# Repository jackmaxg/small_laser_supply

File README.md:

# Swept Source Laser Driver

A small 5v 3mA constant current laser diode power supply for the Physical Optics and Electronics lab, MIT RLE.

Jackson Gray

jackmaxg@mit.edu

Summer '18 UROP

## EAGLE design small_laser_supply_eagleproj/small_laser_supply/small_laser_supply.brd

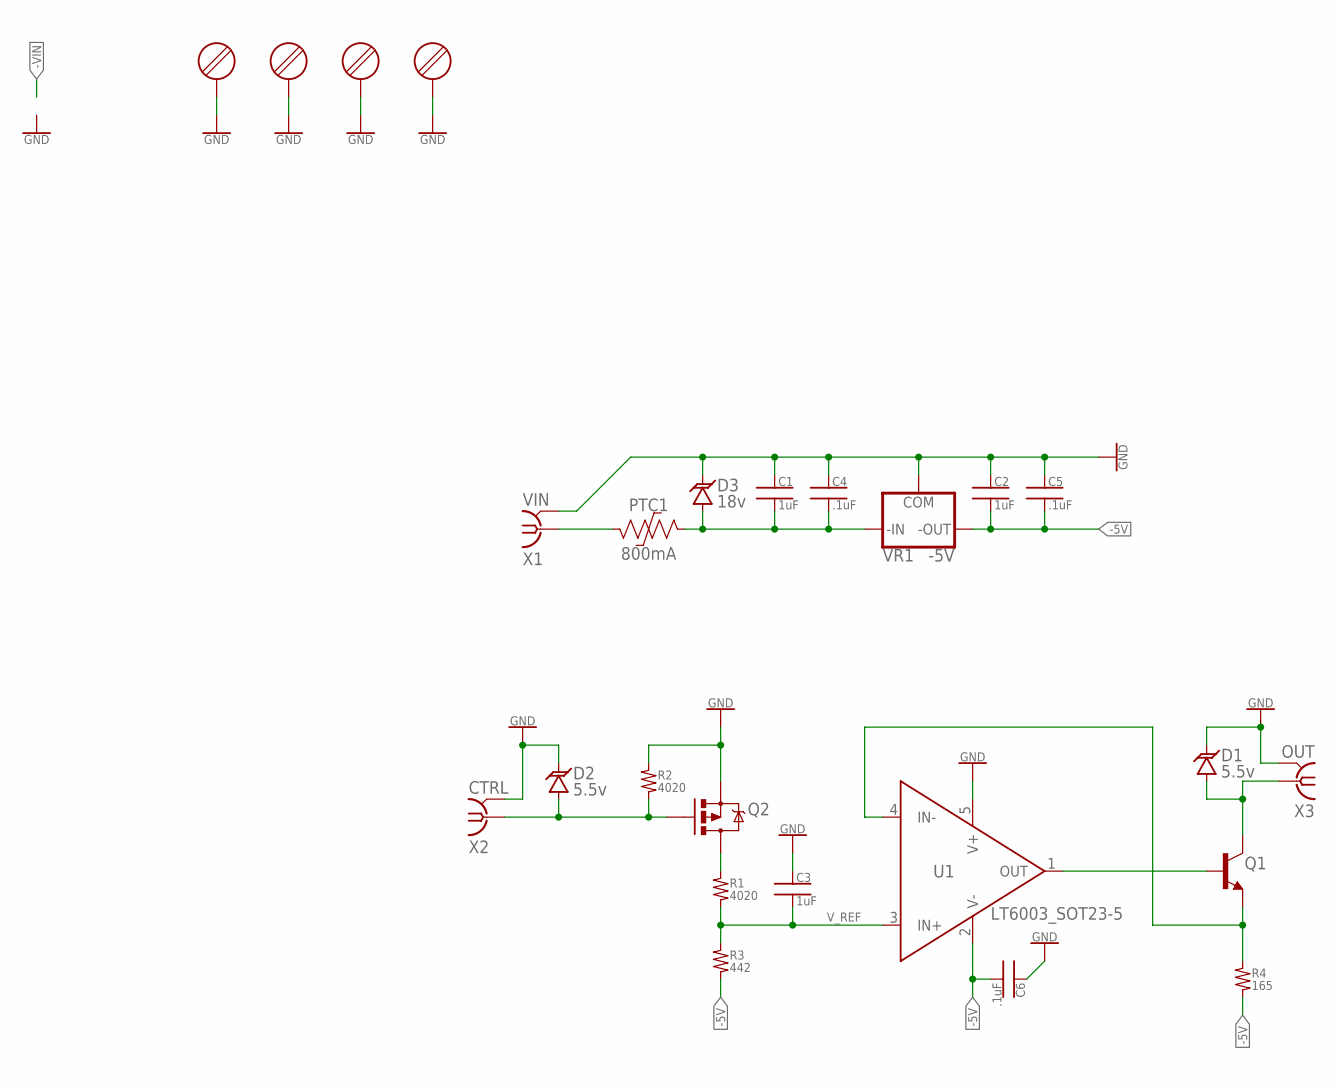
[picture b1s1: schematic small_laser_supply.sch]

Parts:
C1, C2, C3: 1uF; 0603
C4, C5, C6: .1uF; 0603
D1, D2: 5.5v; DO-214AA
D3: 18v; DO-214AA
MH1, MH2, MH3, MH4: THREADED_INSERT_M3; 7466003R
PTC1: 800mA; 2SMD_PTC
Q1: BJT_NPN_SOT23-3; SOT23-3
Q2: MOSFET_P-CHANNEL_SOT23-3; SOT23-3
R1, R2: 4020; 0603
R3: 442; 0603
R4: 165; 0603
U1: LT6003_SOT23-5; SOT23-5
VR1: -5V; DPAK
X1: VIN; 5-1634503-1
X2: CTRL; 5-1634503-1
X3: OUT; 5-1634503-1

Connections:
-5V: C2.2, C5.2, C6.2, R3.2, R4.2, U1.2 (V-), VR1.3 (OUT)
GND: C1.1, C2.1, C3.1, C4.1, C5.1, C6.1, D1.C, D2.C, D3.C, MH1.P, MH2.P, MH3.P, MH4.P, Q2.2 (S), R2.1, U1.5 (V+), VR1.1 (GND), X1.G1 (GND), X1.G2 (GND), X1.G3 (GND), X1.G4 (GND), X2.G1 (GND), X2.G2 (GND), X2.G3 (GND), X2.G4 (GND), X3.G1 (GND), X3.G2 (GND), X3.G3 (GND), X3.G4 (GND)
unnamed: Q1.1 (B), U1.1 (OUT)
unnamed: Q1.2 (E), R4.1, U1.4 (IN-)
unnamed: Q2.3 (D), R1.1
unnamed: PTC1.1, X1.C (1)
unnamed: D1.A, Q1.3 (C), X3.C (1)
unnamed: C1.2, C4.2, D3.A, PTC1.2, VR1.4 (IN)
unnamed: D2.A, Q2.1 (G), R2.2, X2.C (1)
V_REF: C3.2, R1.2, R3.1, U1.3 (IN+)

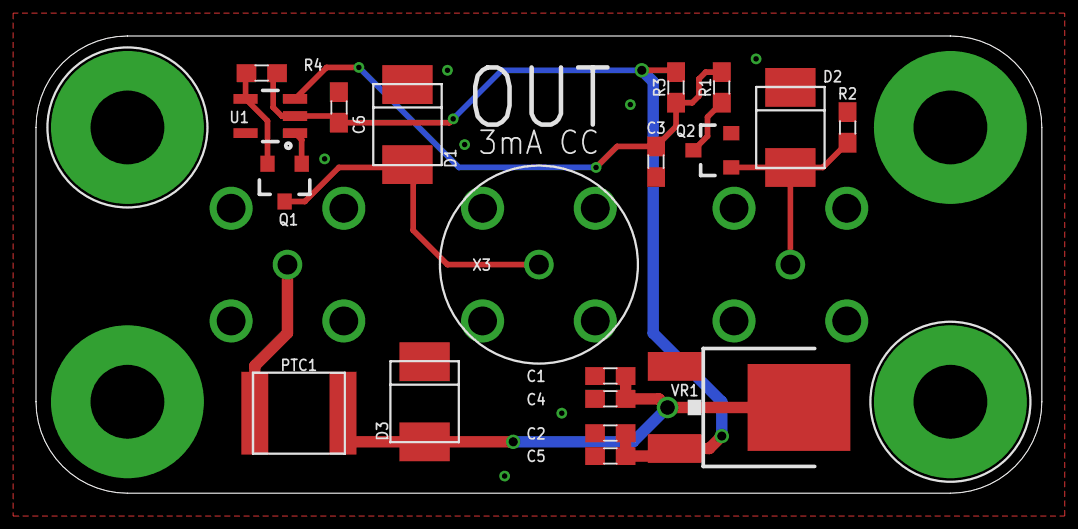
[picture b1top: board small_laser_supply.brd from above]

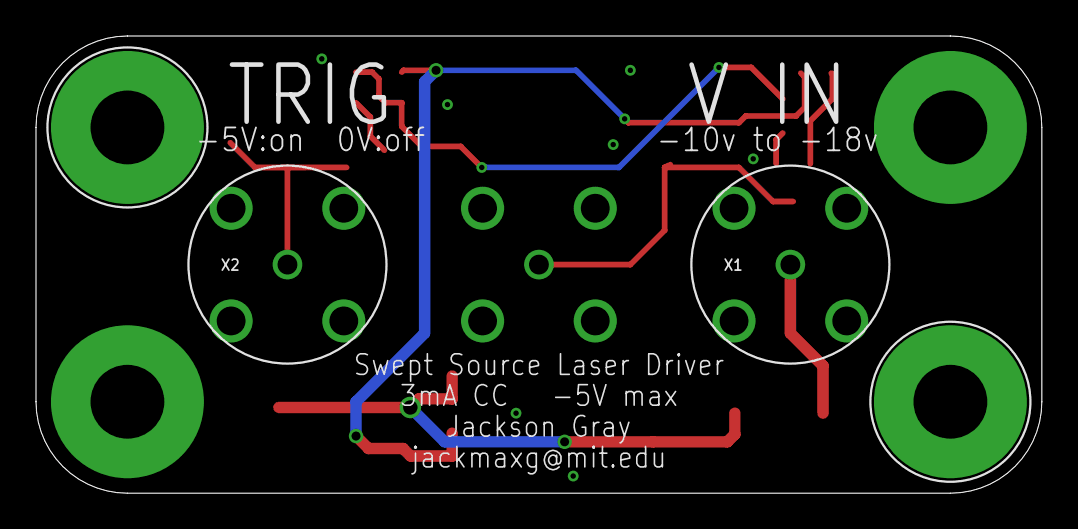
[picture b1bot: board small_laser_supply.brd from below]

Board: 2 copper layers, 55.9 x 25.4 mm, 25 parts (4 on the bottom side), 10 nets.

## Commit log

2018-06-04 Added standard gitattributes and gitignore files to the new project
2018-06-04 Added new project files, schematic, and the project library with a few things in it
2018-06-04 Added a board with the general parts layout, and a general layout of the schematic as well.
2018-06-04 Added a few more bits to the lib, opamp, resistor/capacitor, and a pnp bjt
2018-06-04 Added some Input/Output protection bits to the library
2018-06-05 small tweaks to the library symbols and minor things like that
2018-06-05 Simulated the circuit in LTSpice
2018-06-05 Nearly finished the schematic and initial board layout (before routing traces)
2018-06-05 added a new linear voltage reg and added 0805 package CAP/RES
2018-06-05 lots more work on the board and schematic before realizing the laser diode is actually backwards and we need to pull current out of ground
2018-06-06 simulated the negative voltage circuit version.
2018-06-06 Added a ptc and a Pmos and a few minor bits here and there
2018-06-06 Fixed version of the schematic seems to be finished
2018-06-06 added LTSPICE's .plt files to the .gitignore
2018-06-06 Started and probably finished laying out the board and routing traces, need to generate gerber files next.
2018-06-06 Took a couple images of the board and schematic and added them to the README.md file
2018-06-06 moved things around in the README.md
2018-06-06 Moved the big chunks to the center of the schematic, and took a better picture of it
2018-06-07 generated the cam and gerbers to send to 3pcb, added .cam files as BINARY to .gitattributes
2018-06-07 stuck a resistor across the pfet's gate last min, updated the board and images and gerbers and such
2018-06-07 fixed an issue with too small of vias, updated board and re-gerber-ficated.
2018-06-07 added the BOM
2018-06-08 Created a case for the pcb in cad, and generated two stls for both plates. Made step and stl file types binary in gitattributes
2018-06-08 Tweaked the readme.md bc cad image wasn't showing up, think it has to do with capitalized filetype extensions
2018-06-08 updated the case pic
2018-06-19 Tweaks following the build of the first few boards, this is mostly minor dimensional fixes here and there. Also fixed a bom issue, one of the parts came on a giant reel instead of tape.
